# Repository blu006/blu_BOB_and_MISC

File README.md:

This repository contains my random items that I probably only produced once or twice.

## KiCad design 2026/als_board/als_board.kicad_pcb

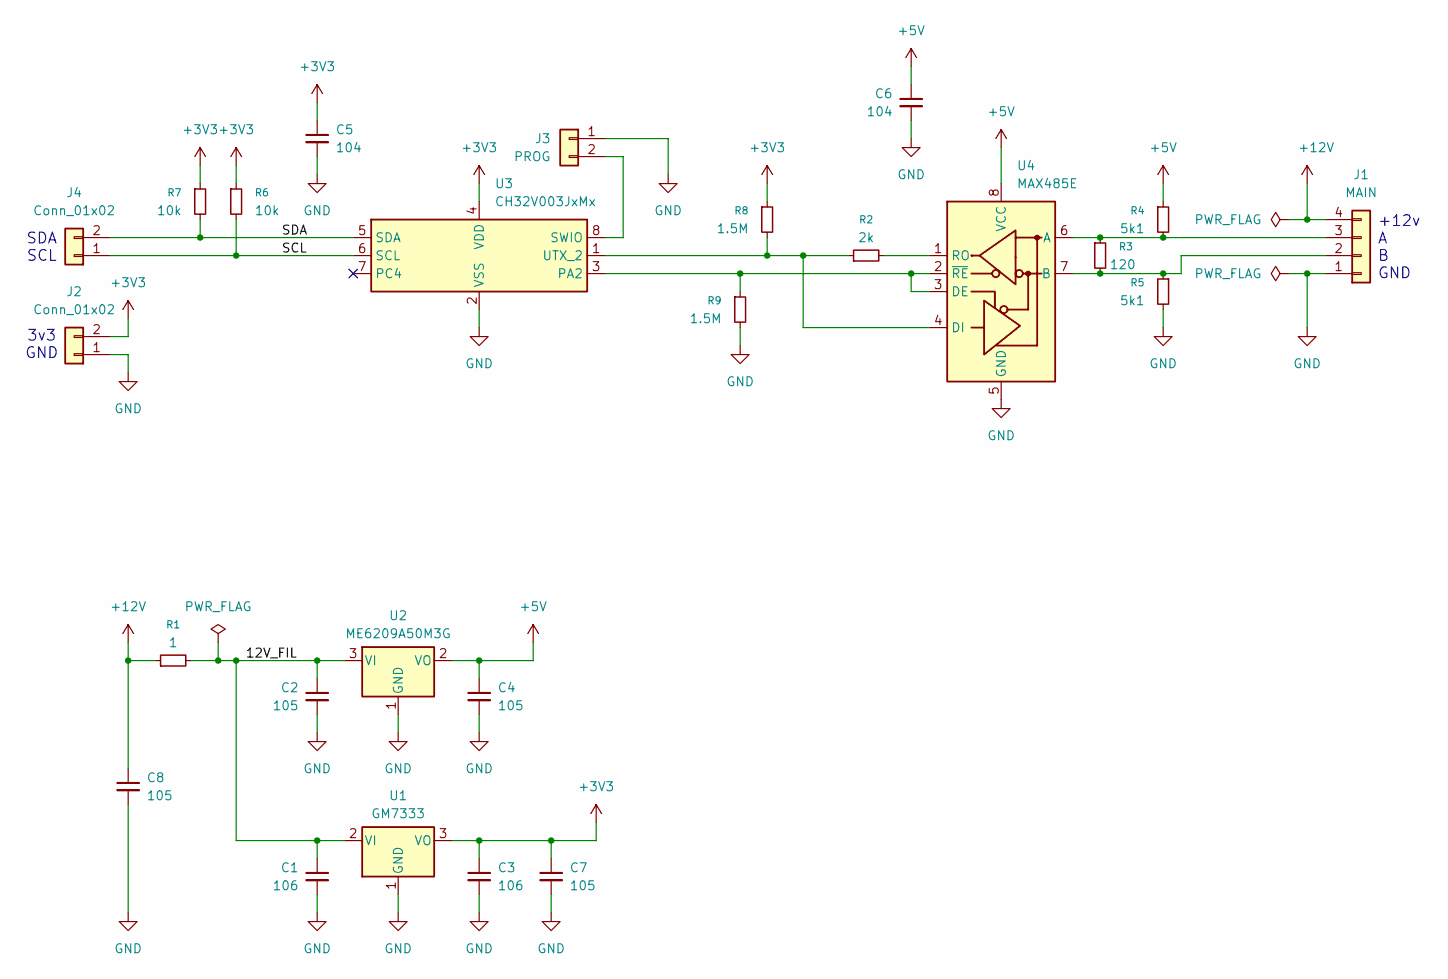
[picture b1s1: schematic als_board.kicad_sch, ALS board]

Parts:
C1, C3: 106; C_1206_3216Metric
C2, C4, C7, C8: 105; C_0805_2012Metric
C5, C6: 104; C_0603_1608Metric
J1: MAIN; PADS_4
J2: Conn_01x02; R_1206_3216Metric
J3: PROG; C_0805_2012Metric
J4: Conn_01x02; R_0805_2012Metric
R1: 1; R_0603_1608Metric
R2: 2k; R_0603_1608Metric
R3: 120; R_0603_1608Metric
R4, R5: 5k1; R_0603_1608Metric
R6, R7: 10k; R_0603_1608Metric
R8, R9: 1.5M; R_0603_1608Metric
U1: GM7333; SOT-89-3
U2: ME6209A50M3G; SOT-23
U3: CH32V003JxMx; JEITA_SOIC-8_3.9x4.9mm_P1.27mm
U4: MAX485E; SOIC-8_3.9x4.9mm_P1.27mm

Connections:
+3V3: C3.1, C5.1, C7.1, J2.2, R6.1, R7.1, R8.1, U1.3 (VO), U3.4 (VDD)
+5V: C4.1, C6.1, R4.1, U2.2 (VO), U4.8 (VCC)
+12V: C8.1, J1.4, R1.1
/12V_FIL: C1.1, C2.1, R1.2, U1.2 (VI), U2.3 (VI)
/SCL: J4.1, R6.2, U3.6 (SCL)
/SDA: J4.2, R7.2, U3.5 (SDA)
GND: C1.2, C2.2, C3.2, C4.2, C5.2, C6.2, C7.2, C8.2, J1.1, J2.1, J3.1, R5.2, R9.2, U1.1 (GND), U2.1 (GND), U3.2 (VSS), U4.5 (GND)
unnamed: J1.2, R3.2, R5.1, U4.7 (B)
unnamed: J1.3, R3.1, R4.2, U4.6 (A)
unnamed: J3.2, U3.8 (SWIO)
unnamed: R9.1, U3.3 (PA2), U4.2 (~RE), U4.3 (DE)
unnamed: R2.1, R8.2, U3.1 (UTX_2), U4.4 (DI)
unnamed: R2.2, U4.1 (RO)

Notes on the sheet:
3v3 GND
+12v A B GND
SDA SCL

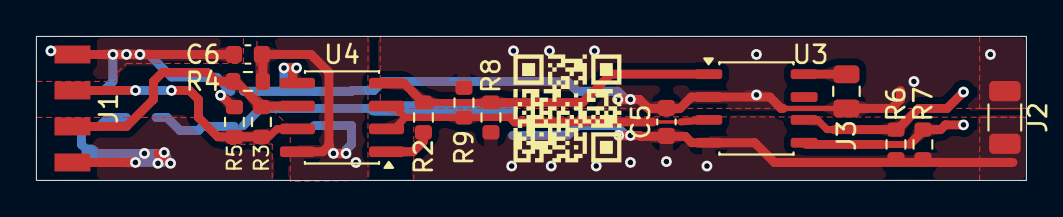
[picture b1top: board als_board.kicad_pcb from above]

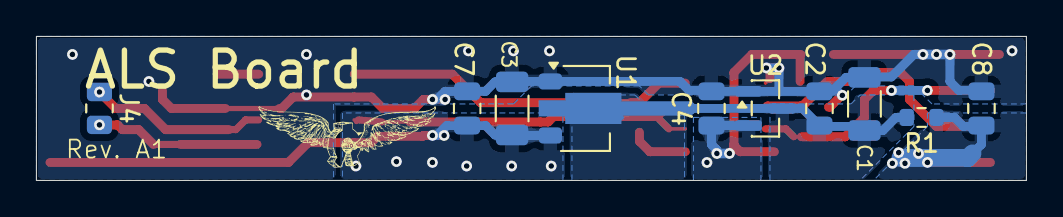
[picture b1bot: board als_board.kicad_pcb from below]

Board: 2 copper layers, 55.0 x 8.0 mm, 25 parts (10 on the bottom side), 13 nets.

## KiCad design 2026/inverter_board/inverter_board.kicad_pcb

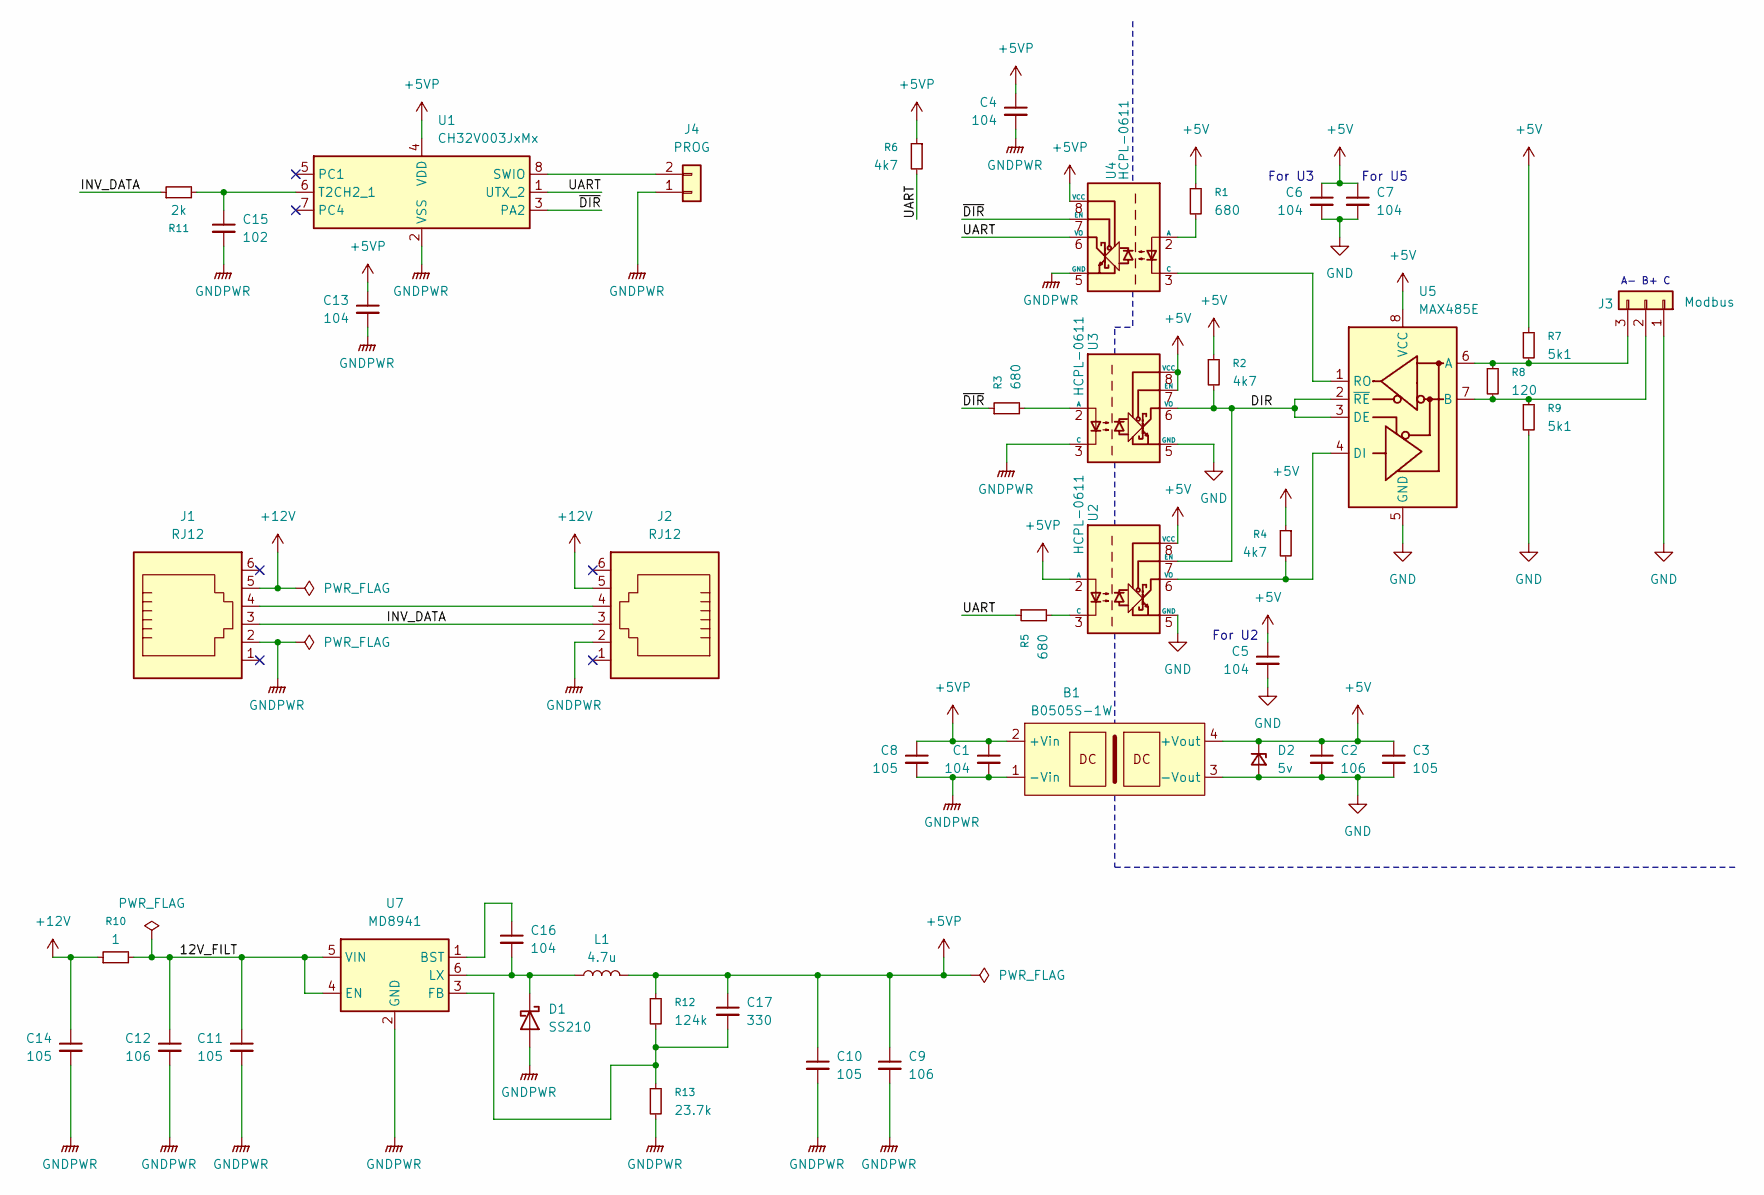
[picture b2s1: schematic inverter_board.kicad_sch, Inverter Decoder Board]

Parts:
B1: B0505S-1W; BxxxxS-1W
C1, C4, C5, C6, C7, C13, C16: 104; C_0603_1608Metric
C2, C9, C12: 106; C_1206_3216Metric
C3, C8, C10, C11, C14: 105; C_0805_2012Metric
C15: 102; C_0603_1608Metric
C17: 330; C_0603_1608Metric
D1: SS210; D_SMA
D2: 5v; D_SMB
J1, J2: RJ12; RJ25_Wayconn_MJEA-660X1_Horizontal
J3: Modbus; TerminalBlock_Phoenix_MKDS-3-3-5.08_1x03_P5.08mm_Horizontal
J4: PROG; R_0805_2012Metric
L1: 4.7u; L_APV_APH0420
R1, R3, R5: 680; R_0603_1608Metric
R2, R4, R6: 4k7; R_0603_1608Metric
R7, R9: 5k1; R_0603_1608Metric
R8: 120; R_0603_1608Metric
R10: 1; R_0603_1608Metric
R11: 2k; R_0603_1608Metric
R12: 124k; R_0603_1608Metric
R13: 23.7k; R_0603_1608Metric
U1: CH32V003JxMx; JEITA_SOIC-8_3.9x4.9mm_P1.27mm
U2, U3, U4: HCPL-0611; SOIC-8_3.9x4.9mm_P1.27mm
U5: MAX485E; SOIC-8_3.9x4.9mm_P1.27mm
U7: MD8941; SOT-23-6

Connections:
+5V: B1.4 (+Vout), C2.1, C3.1, C5.1, C6.1, C7.1, D2.1 (K), R1.1, R2.1, R4.1, R7.1, U2.8 (VCC), U3.7 (EN), U3.8 (VCC), U5.8 (VCC)
+5VP: B1.2 (+Vin), C1.1, C4.1, C8.1, C9.1, C10.1, C13.1, C17.1, L1.2, R6.1, R12.1, U1.4 (VDD), U2.2 (A), U4.8 (VCC)
+12V: C14.1, J1.5, J2.5, R10.1
/12V_FILT: C11.1, C12.1, R10.2, U7.4 (EN), U7.5 (VIN)
/DIR: R2.2, U2.7 (EN), U3.6 (VO), U5.2 (~RE), U5.3 (DE)
/INV_DATA: J1.3, J2.3, R11.1
/UART: R5.1, R6.2, U1.1 (UTX_2), U4.6 (VO)
/~DIR: R3.1, U1.3 (PA2), U4.7 (EN)
GND: B1.3 (-Vout), C2.2, C3.2, C5.2, C6.2, C7.2, D2.2 (A), J3.1, R9.2, U2.5 (GND), U3.5 (GND), U5.5 (GND)
GNDPWR: B1.1 (-Vin), C1.2, C4.2, C8.2, C9.2, C10.2, C11.2, C12.2, C13.2, C14.2, C15.2, D1.2 (A), J1.2, J2.2, J4.1, R13.2, U1.2 (VSS), U3.3 (C), U4.5 (GND), U7.2 (GND)
unnamed: C16.2, D1.1 (K), L1.1, U7.6 (LX)
unnamed: J1.4, J2.4
unnamed: J3.2, R8.2, R9.1, U5.7 (B)
unnamed: J3.3, R7.2, R8.1, U5.6 (A)
unnamed: J4.2, U1.8 (SWIO)
unnamed: C15.1, R11.2, U1.6 (T2CH2_1)
unnamed: R5.2, U2.3 (C)
unnamed: R4.2, U2.6 (VO), U5.4 (DI)
unnamed: R3.2, U3.2 (A)
unnamed: R1.2, U4.2 (A)
unnamed: U4.3 (C), U5.1 (RO)
unnamed: C16.1, U7.1 (BST)
unnamed: C17.2, R12.2, R13.1, U7.3 (FB)

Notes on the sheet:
For U5
For U3
A- B+ C
For U2

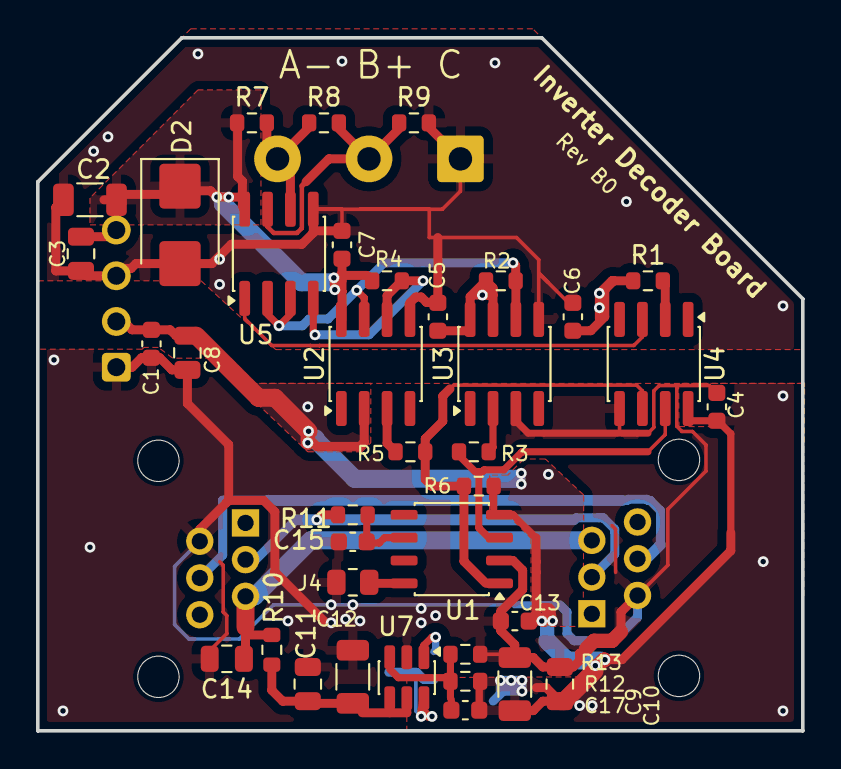
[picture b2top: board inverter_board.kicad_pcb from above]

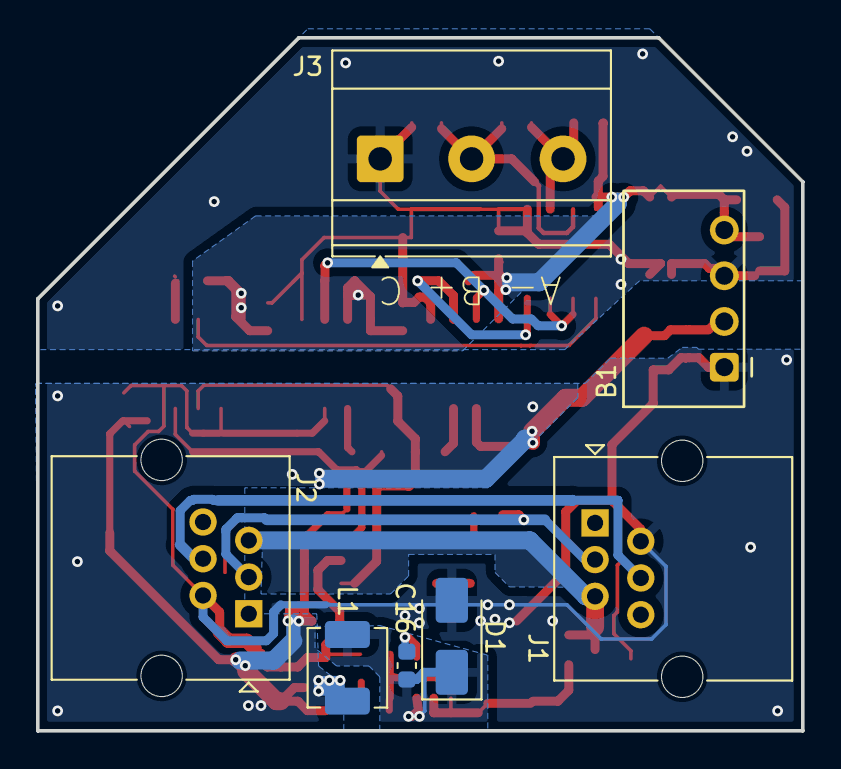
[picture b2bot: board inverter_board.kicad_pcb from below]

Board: 2 copper layers, 42.5 x 38.5 mm, 44 parts (7 on the bottom side), 23 nets.

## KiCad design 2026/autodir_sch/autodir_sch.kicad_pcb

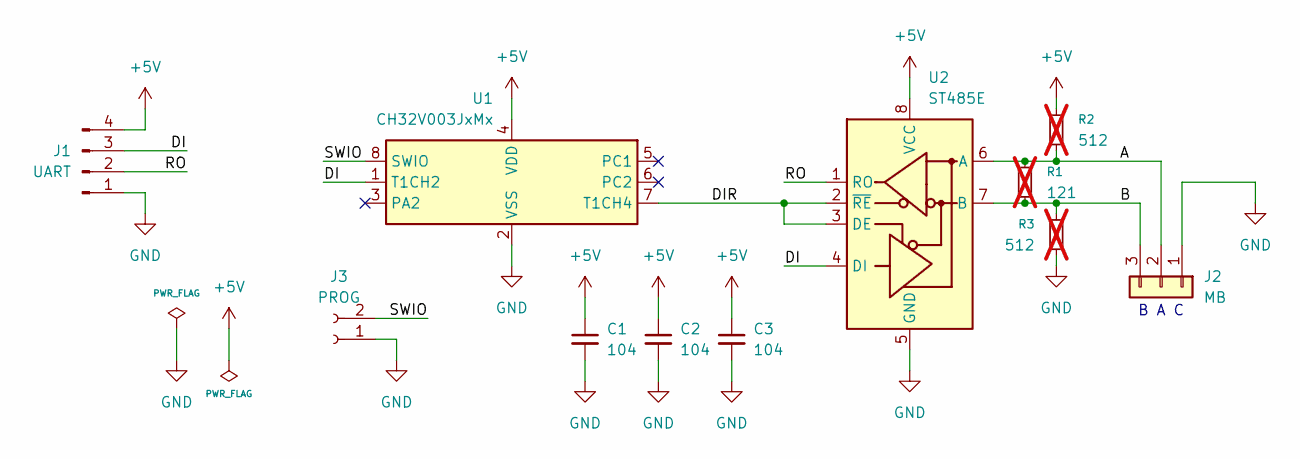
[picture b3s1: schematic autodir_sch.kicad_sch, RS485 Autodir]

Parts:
C1, C2, C3: 104; C_0603_1608Metric
J1: UART; PinHeader_1x04_P2.54mm_Horizontal
J2: MB; TerminalBlock_Phoenix_MKDS-1,5-3-5.08_1x03_P5.08mm_Horizont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
J3: PROG; R_0805_2012Metric
R1: 121; R_0603_1608Metric; not fitted
R2, R3: 512; R_0603_1608Metric; not fitted
U1: CH32V003JxMx; JEITA_SOIC-8_3.9x4.9mm_P1.27mm
U2: ST485E; SOIC-8_3.9x4.9mm_P1.27mm

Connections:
+5V: C1.1, C2.1, C3.1, J1.4, R2.1, U1.4 (VDD), U2.8 (VCC)
/A: J2.2, R1.1, R2.2, U2.6 (A)
/B: J2.3, R1.2, R3.1, U2.7 (B)
/DI: J1.3, U1.1 (T1CH2), U2.4 (DI)
/DIR: U1.7 (T1CH4), U2.2 (~RE), U2.3 (DE)
/RO: J1.2, U2.1 (RO)
/SWIO: J3.2, U1.8 (SWIO)
GND: C1.2, C2.2, C3.2, J1.1, J2.1, J3.1, R3.2, U1.2 (VSS), U2.5 (GND)

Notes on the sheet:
B A C

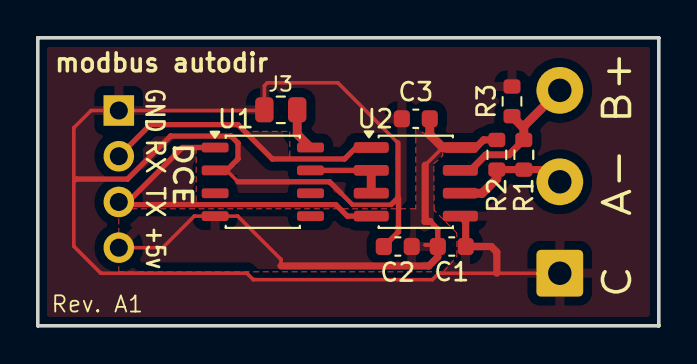
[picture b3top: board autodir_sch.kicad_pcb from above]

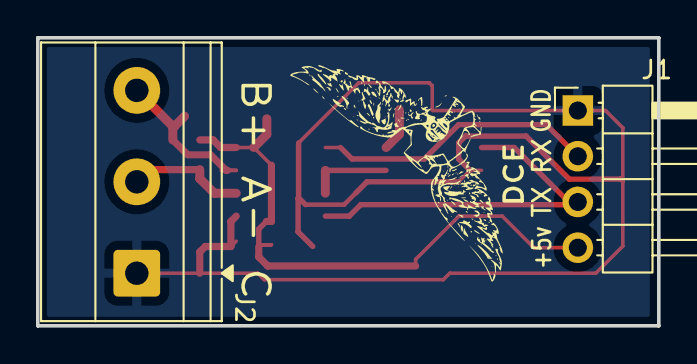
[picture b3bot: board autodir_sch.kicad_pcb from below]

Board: 2 copper layers, 34.5 x 16.0 mm, 11 parts (2 on the bottom side), 8 nets.

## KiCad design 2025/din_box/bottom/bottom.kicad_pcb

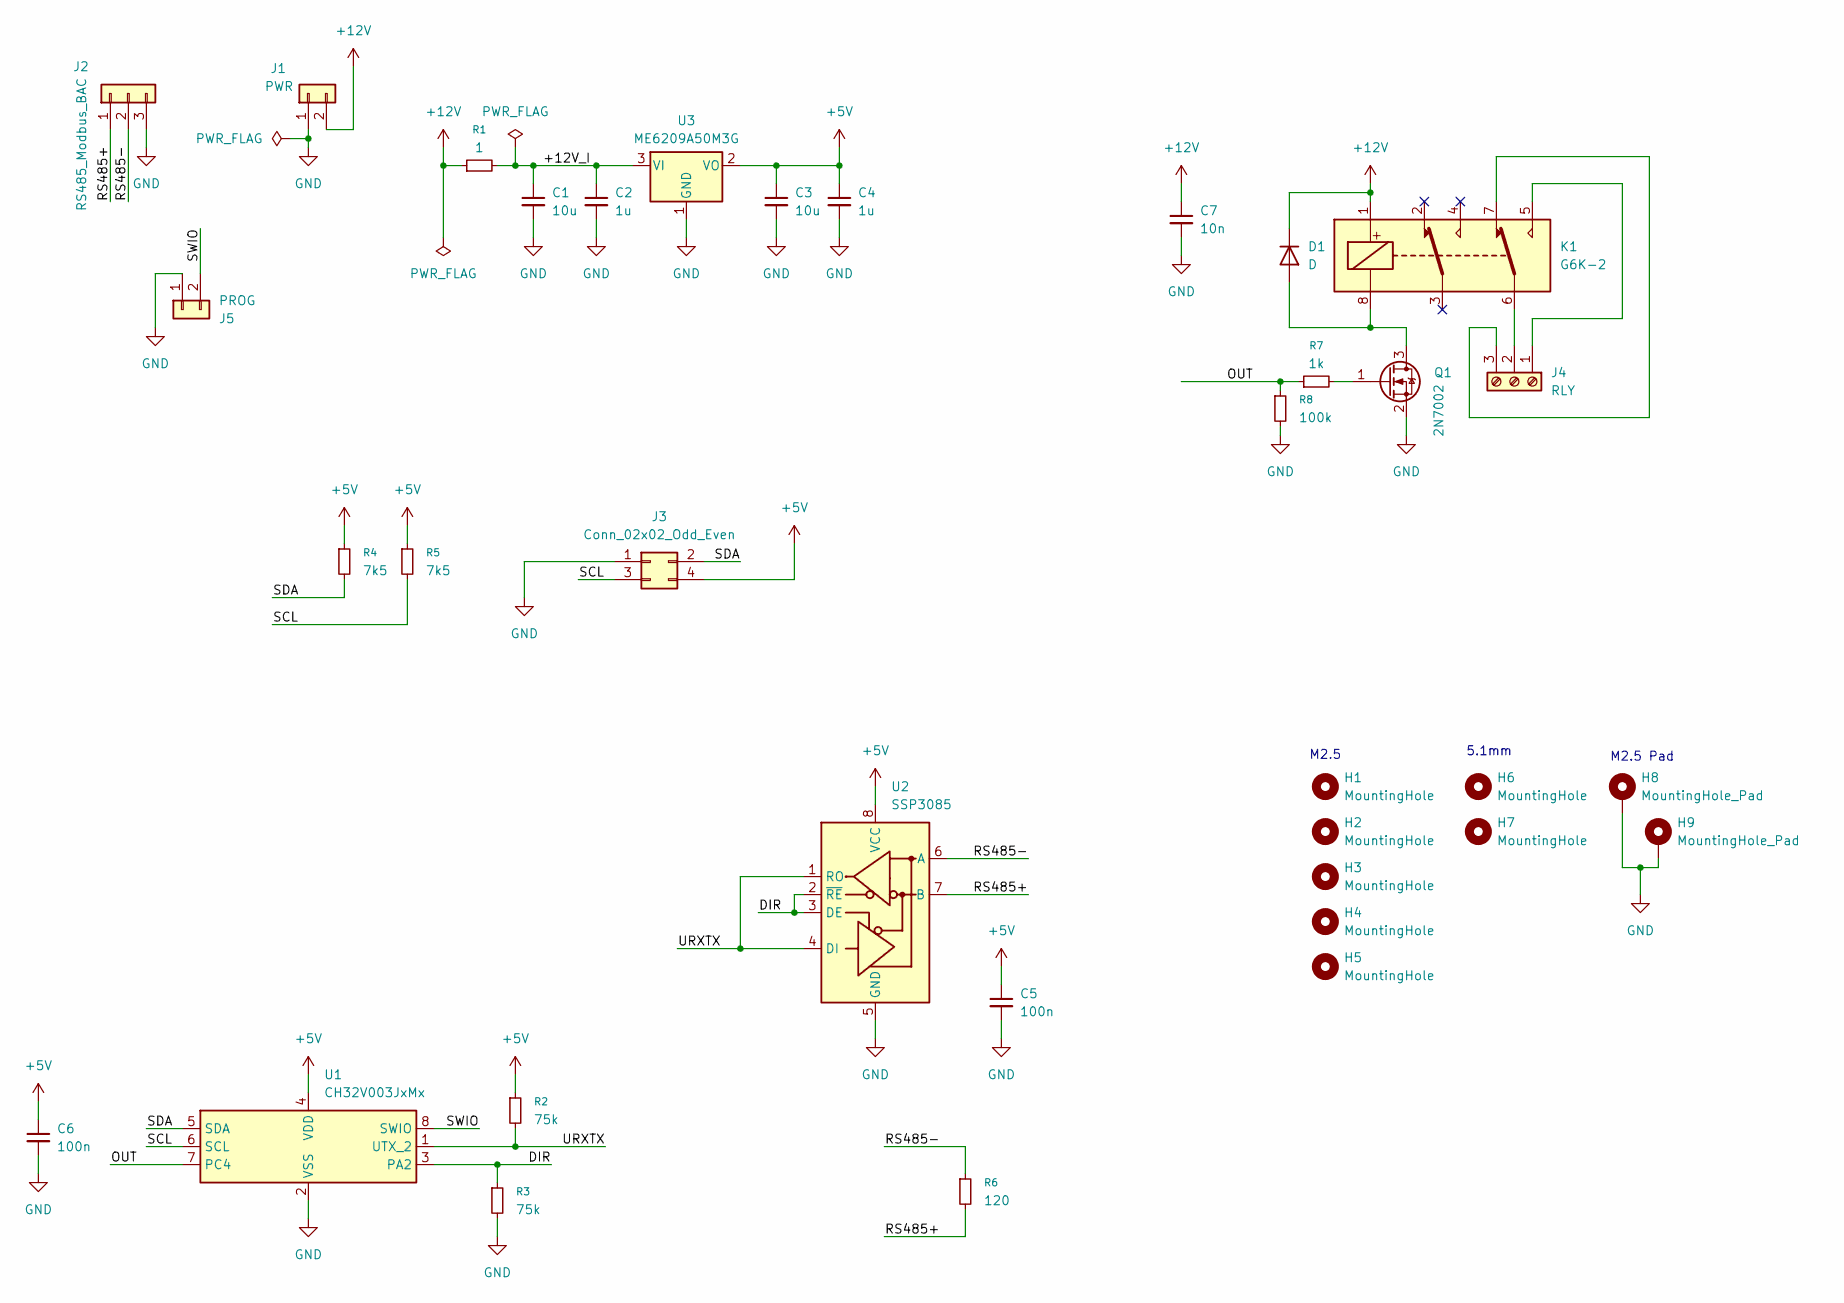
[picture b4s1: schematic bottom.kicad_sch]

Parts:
C1, C3: 10u; C_1206_3216Metric
C2, C4: 1u; C_0805_2012Metric
C5, C6: 100n; C_0603_1608Metric
C7: 10n; C_0603_1608Metric
D1: D; D_MELF
H1, H2, H3, H4, H5: MountingHole; MountingHole_2.7mm_M2.5_ISO7380
H6, H7: MountingHole; MountingHole_5.3mm_M5_ISO7380
H8, H9: MountingHole_Pad; MountingHole_2.7mm_M2.5_ISO7380_Pad
J1: PWR; TerminalBlock_Phoenix_MKDS-1,5-2-5.08_1x02_P5.08mm_Horizont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
J2: RS485_Modbus_BAC; TerminalBlock_Phoenix_MKDS-1,5-3-5.08_1x03_P5.08mm_Horizont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
J3: Conn_02x02_Odd_Even; PinHeader_2x02_P2.54mm_Vertical
J4: RLY; TerminalBlock_Phoenix_MKDS-1,5-3-5.08_1x03_P5.08mm_Horizont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
J5: PROG; PinHeader_1x02_P2.54mm_Vertical
K1: G6K-2; Relay_DPDT_Omron_G6K-2F-Y
Q1: 2N7002; SOT-23
R1: 1; R_0603_1608Metric
R2, R3: 75k; R_0603_1608Metric
R4, R5: 7k5; R_0603_1608Metric
R6: 120; R_0603_1608Metric
R7: 1k; R_0603_1608Metric
R8: 100k; R_0402_1005Metric
U1: CH32V003JxMx; SOP-8_3.9x4.9mm_P1.27mm
U2: SSP3085; SOIC-8_3.9x4.9mm_P1.27mm
U3: ME6209A50M3G; SOT-23

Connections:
+5V: C3.1, C4.1, C5.1, C6.1, J3.4, R2.1, R4.1, R5.1, U1.4 (VDD), U2.8 (VCC), U3.2 (VO)
+12V: C7.1, D1.1 (K), J1.2, K1.1, R1.1
/+12V_I: C1.1, C2.1, R1.2, U3.3 (VI)
/DIR: R3.1, U1.3 (PA2), U2.2 (~RE), U2.3 (DE)
/OUT: R7.1, R8.1, U1.7 (PC4)
/RS485+: J2.1, R6.2, U2.7 (B)
/RS485-: J2.2, R6.1, U2.6 (A)
/SCL: J3.3, R5.2, U1.6 (SCL)
/SDA: J3.2, R4.2, U1.5 (SDA)
/SWIO: J5.2, U1.8 (SWIO)
/URXTX: R2.2, U1.1 (UTX_2), U2.1 (RO), U2.4 (DI)
GND: C1.2, C2.2, C3.2, C4.2, C5.2, C6.2, C7.2, H8.1, H9.1, J1.1, J2.3, J3.1, J5.1, Q1.2 (S), R3.2, R8.2, U1.2 (VSS), U2.5 (GND), U3.1 (GND)
unnamed: D1.2 (A), K1.8, Q1.3 (D)
unnamed: J4.1, K1.5
unnamed: J4.2, K1.6
unnamed: J4.3, K1.7
unnamed: Q1.1 (G), R7.2

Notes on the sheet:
M2.5 Pad
5.1mm
M2.5

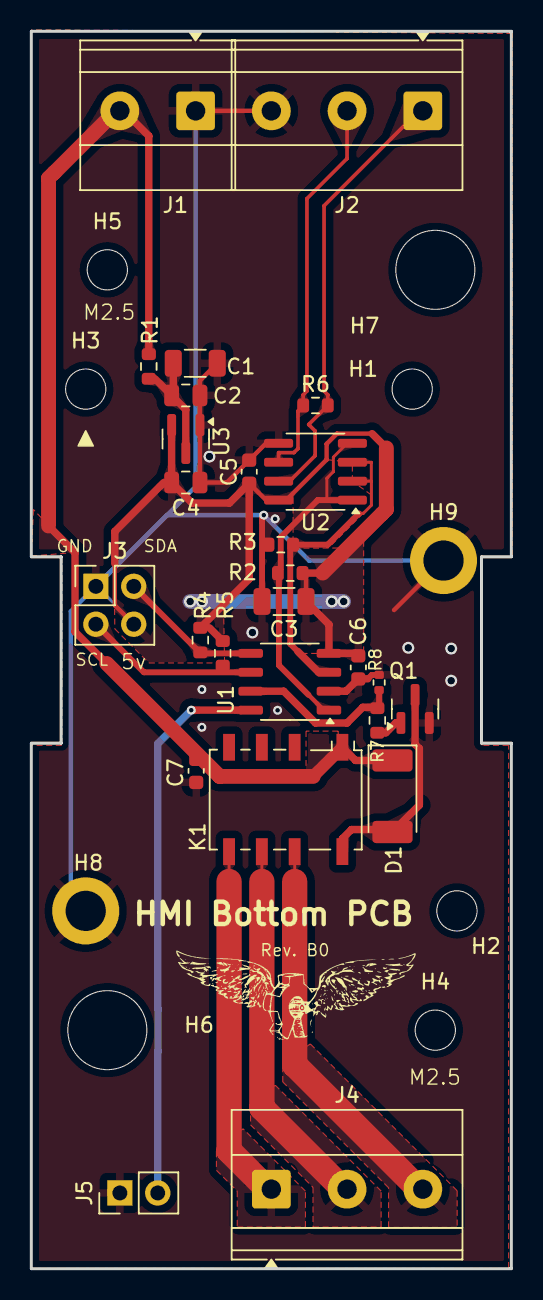
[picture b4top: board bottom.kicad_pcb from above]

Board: 2 copper layers, 32.2 x 83.0 mm, 36 parts (1 on the bottom side), 17 nets.

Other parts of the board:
QR1: MAGLab Website

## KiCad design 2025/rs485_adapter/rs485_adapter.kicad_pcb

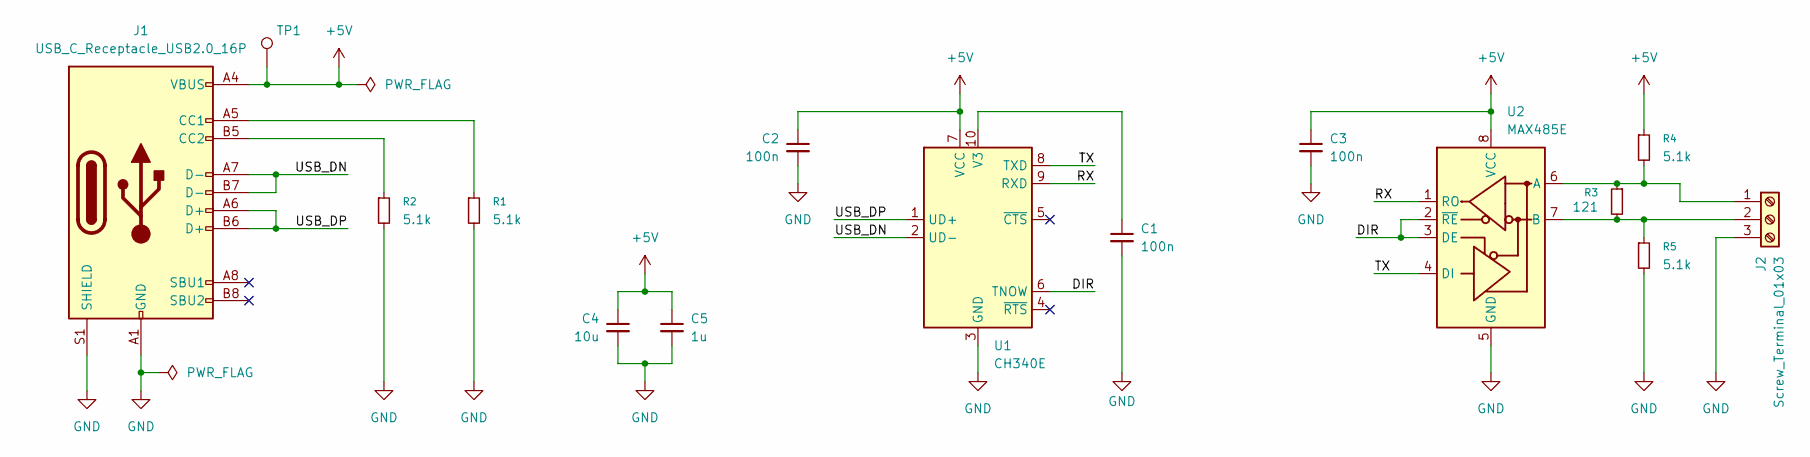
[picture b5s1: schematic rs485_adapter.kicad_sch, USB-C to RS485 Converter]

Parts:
C1, C2, C3: 100n; C_0603_1608Metric
C4: 10u; C_1206_3216Metric
C5: 1u; C_0805_2012Metric
J1: USB_C_Receptacle_USB2.0_16P; USB_C_Receptacle_XKB_U262-16XN-4BVC11
J2: Screw_Terminal_01x03; TerminalBlock_Phoenix_MKDS-1,5-3-5.08_1x03_P5.08mm_Horizont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
R1, R2, R4, R5: 5.1k; R_0603_1608Metric
R3: 121; R_0603_1608Metric
TP1: TestPoint; TestPoint_Pad_1.0x1.0mm
U1: CH340E; MSOP-10_3x3mm_P0.5mm
U2: MAX485E; SOIC-8_3.9x4.9mm_P1.27mm

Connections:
+5V: C2.1, C3.1, C4.1, C5.1, J1.A4 (VBUS), J1.A9 (VBUS), J1.B4 (VBUS), J1.B9 (VBUS), R4.1, TP1.1, U1.7 (VCC), U2.8 (VCC)
/DIR: U1.6 (TNOW), U2.2 (~RE), U2.3 (DE)
/RX: U1.9 (RXD), U2.1 (RO)
/TX: U1.8 (TXD), U2.4 (DI)
/USB_DN: J1.A7 (D-), J1.B7 (D-), U1.2 (UD-)
/USB_DP: J1.A6 (D+), J1.B6 (D+), U1.1 (UD+)
GND: C1.2, C2.2, C3.2, C4.2, C5.2, J1.A1 (GND), J1.A12 (GND), J1.B1 (GND), J1.B12 (GND), J1.S1 (SHIELD), J2.3, R1.2, R2.2, R5.2, U1.3 (GND), U2.5 (GND)
unnamed: J1.A5 (CC1), R1.1
unnamed: J1.B5 (CC2), R2.1
unnamed: J2.1, R3.1, R4.2, U2.6 (A)
unnamed: J2.2, R3.2, R5.1, U2.7 (B)
unnamed: C1.1, U1.10 (V3)

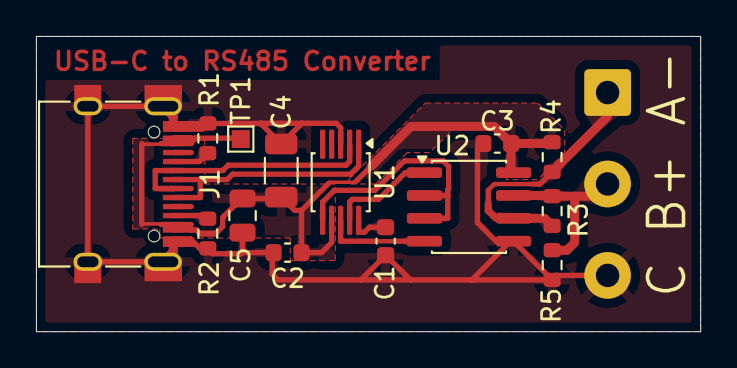
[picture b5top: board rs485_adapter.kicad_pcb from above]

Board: 2 copper layers, 36.9 x 16.4 mm, 15 parts (1 on the bottom side), 12 nets.

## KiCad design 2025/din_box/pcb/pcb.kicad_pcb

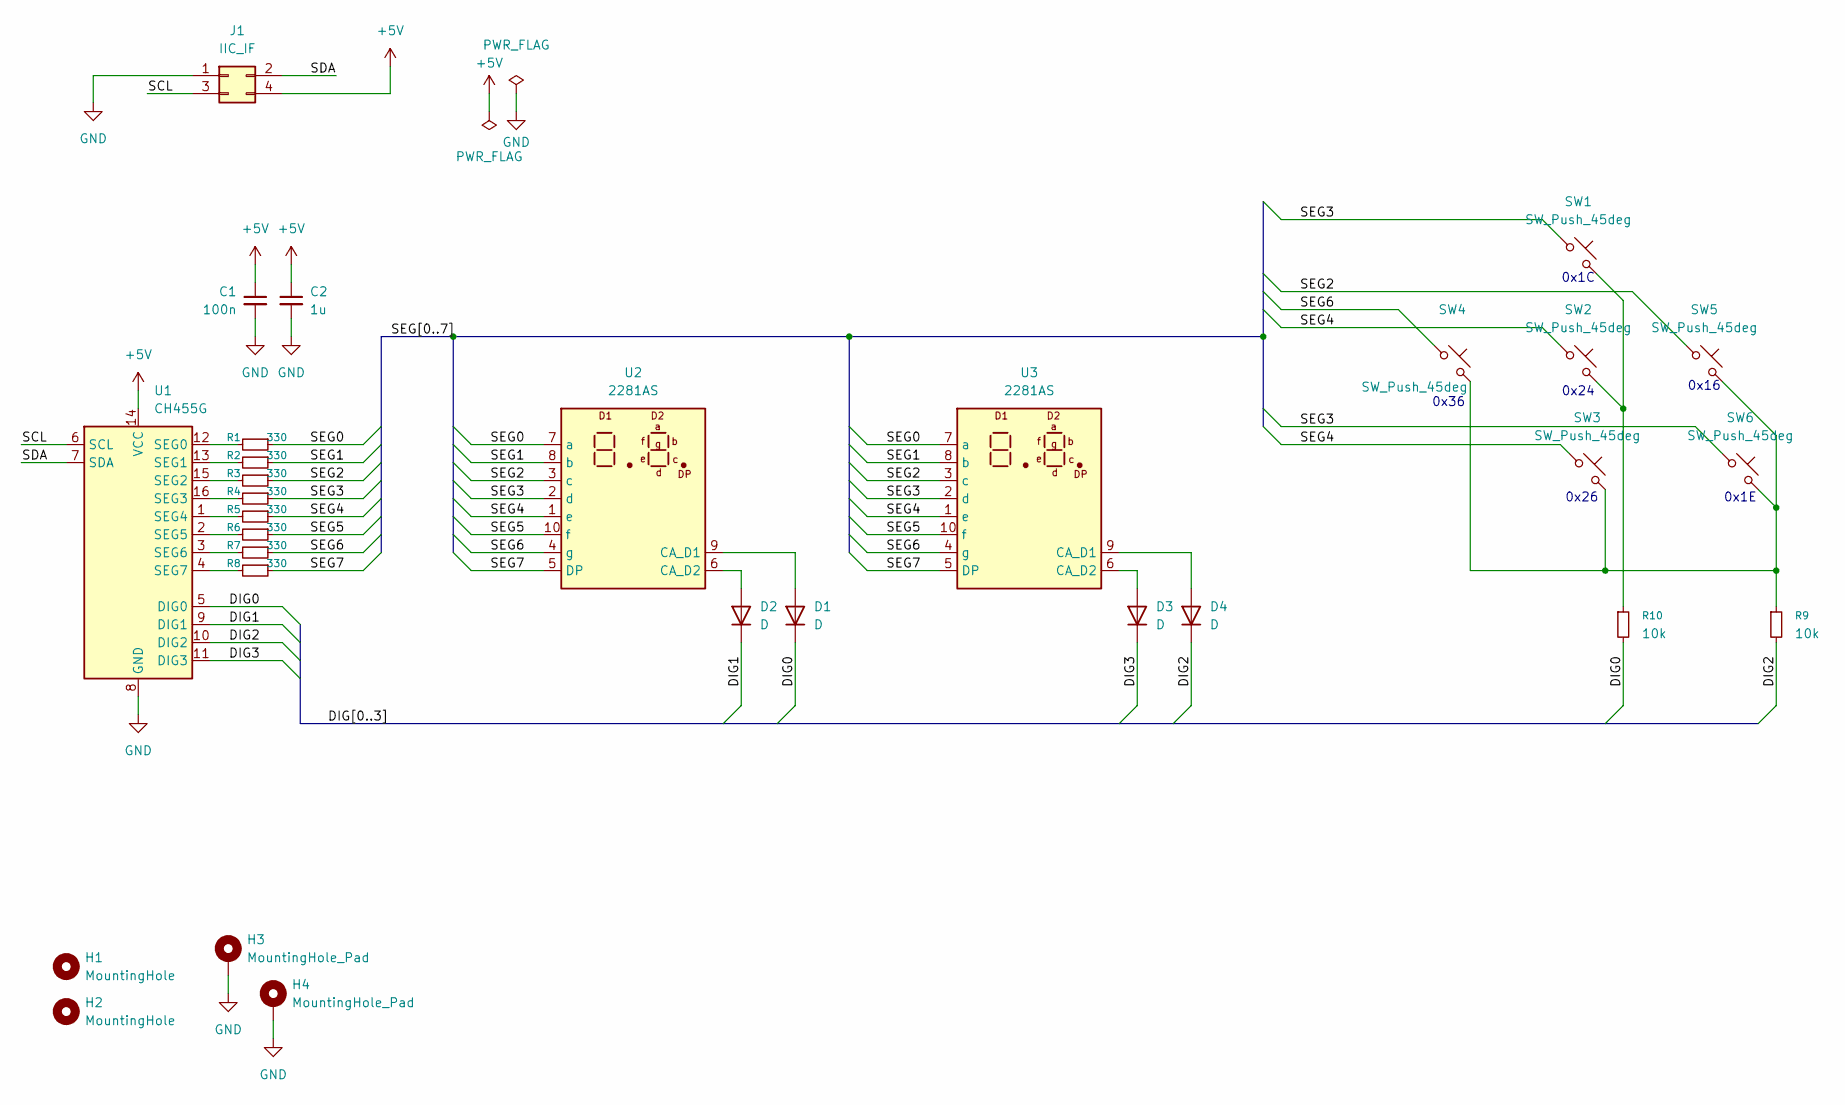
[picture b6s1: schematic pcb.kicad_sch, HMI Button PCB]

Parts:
C1: 100n; C_0603_1608Metric
C2: 1u; C_0805_2012Metric
D1, D2, D3, D4: D; D_SOD-323
H1, H2: MountingHole; MountingHole_2.7mm_M2.5_ISO7380
H3, H4: MountingHole_Pad; MountingHole_2.7mm_M2.5_ISO14580_Pad_TopBottom
J1: IIC_IF; PinSocket_2x02_P2.54mm_Vertical
R1, R2, R3, R4, R5, R6, R7, R8: 330; R_0603_1608Metric
R9, R10: 10k; R_0603_1608Metric
SW1, SW2, SW3, SW4, SW5, SW6: SW_Push_45deg; SW_SPST_PTS810
U1: CH455G; SOP-16_3.9x9.9mm_P1.27mm
U2, U3: 2281AS; 7seg_2dig

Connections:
+5V: C1.1, C2.1, J1.4, U1.14 (VCC)
/DIG0: D1.1 (K), R10.2, U1.5 (DIG0)
/DIG1: D2.1 (K), U1.9 (DIG1)
/DIG2: D4.1 (K), R9.2, U1.10 (DIG2)
/DIG3: D3.1 (K), U1.11 (DIG3)
/SCL: J1.3, U1.6 (SCL)
/SDA: J1.2, U1.7 (SDA)
/SEG0: R1.1, U2.7 (a), U3.7 (a)
/SEG1: R2.1, U2.8 (b), U3.8 (b)
/SEG2: R3.1, SW5.1, U2.3 (c), U3.3 (c)
/SEG3: R4.1, SW1.1, SW6.1, U2.2 (d), U3.2 (d)
/SEG4: R5.1, SW2.1, SW3.1, U2.1 (e), U3.1 (e)
/SEG5: R6.1, U2.10 (f), U3.10 (f)
/SEG6: R7.1, SW4.1, U2.4 (g), U3.4 (g)
/SEG7: R8.1, U2.5 (DP), U3.5 (DP)
GND: C1.2, C2.2, H3.1, H4.1, J1.1, U1.8 (GND)
unnamed: D1.2 (A), U2.9 (CA_D1)
unnamed: D2.2 (A), U2.6 (CA_D2)
unnamed: D3.2 (A), U3.6 (CA_D2)
unnamed: D4.2 (A), U3.9 (CA_D1)
unnamed: R9.1, SW3.2, SW4.2, SW5.2, SW6.2
unnamed: R10.1, SW1.2, SW2.2
unnamed: R1.2, U1.12 (SEG0)
unnamed: R2.2, U1.13 (SEG1)
unnamed: R3.2, U1.15 (SEG2)
unnamed: R4.2, U1.16 (SEG3)
unnamed: R5.2, U1.1 (SEG4)
unnamed: R6.2, U1.2 (SEG5)
unnamed: R7.2, U1.3 (SEG6)
unnamed: R8.2, U1.4 (SEG7)

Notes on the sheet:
0x1E
0x26
0x36
0x1C
0x16
0x24

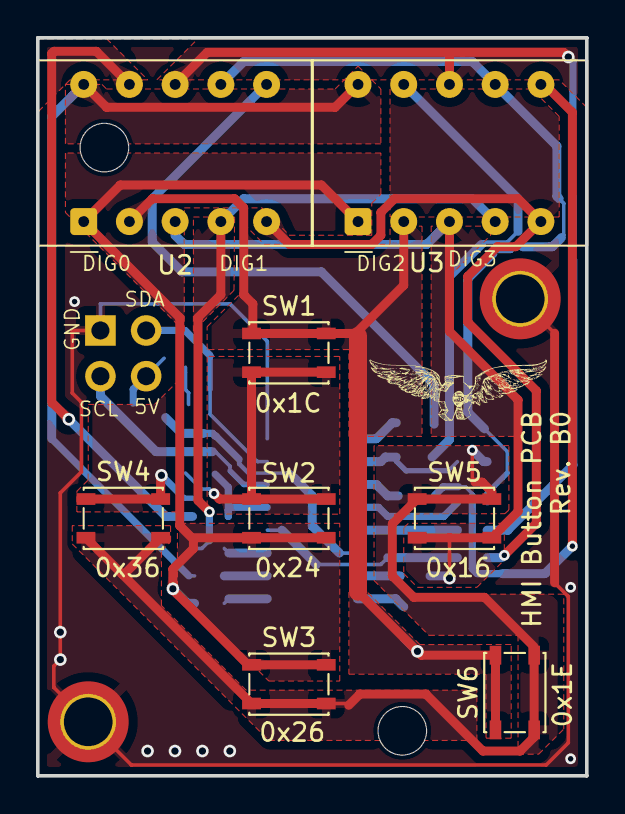
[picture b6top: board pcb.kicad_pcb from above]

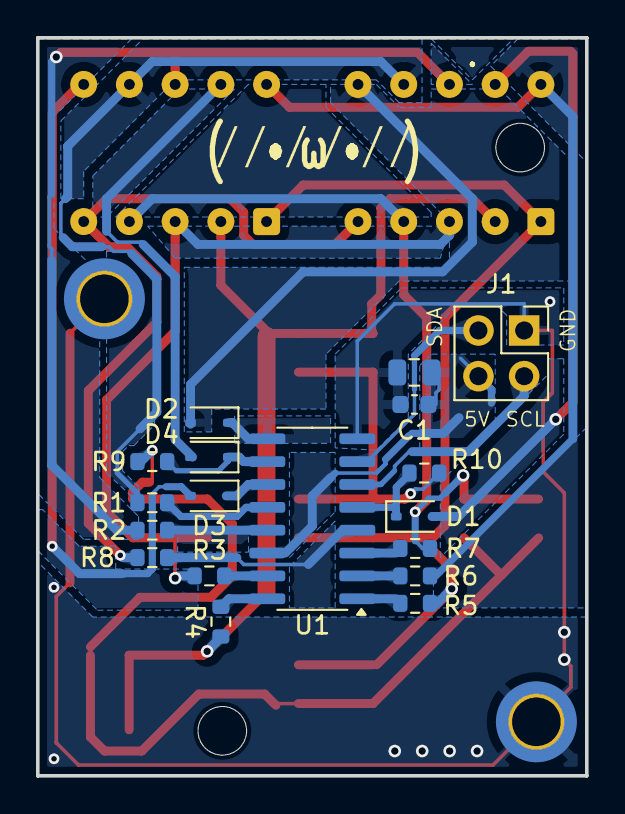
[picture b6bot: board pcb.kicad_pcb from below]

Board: 2 copper layers, 30.5 x 41.0 mm, 30 parts (19 on the bottom side), 30 nets.

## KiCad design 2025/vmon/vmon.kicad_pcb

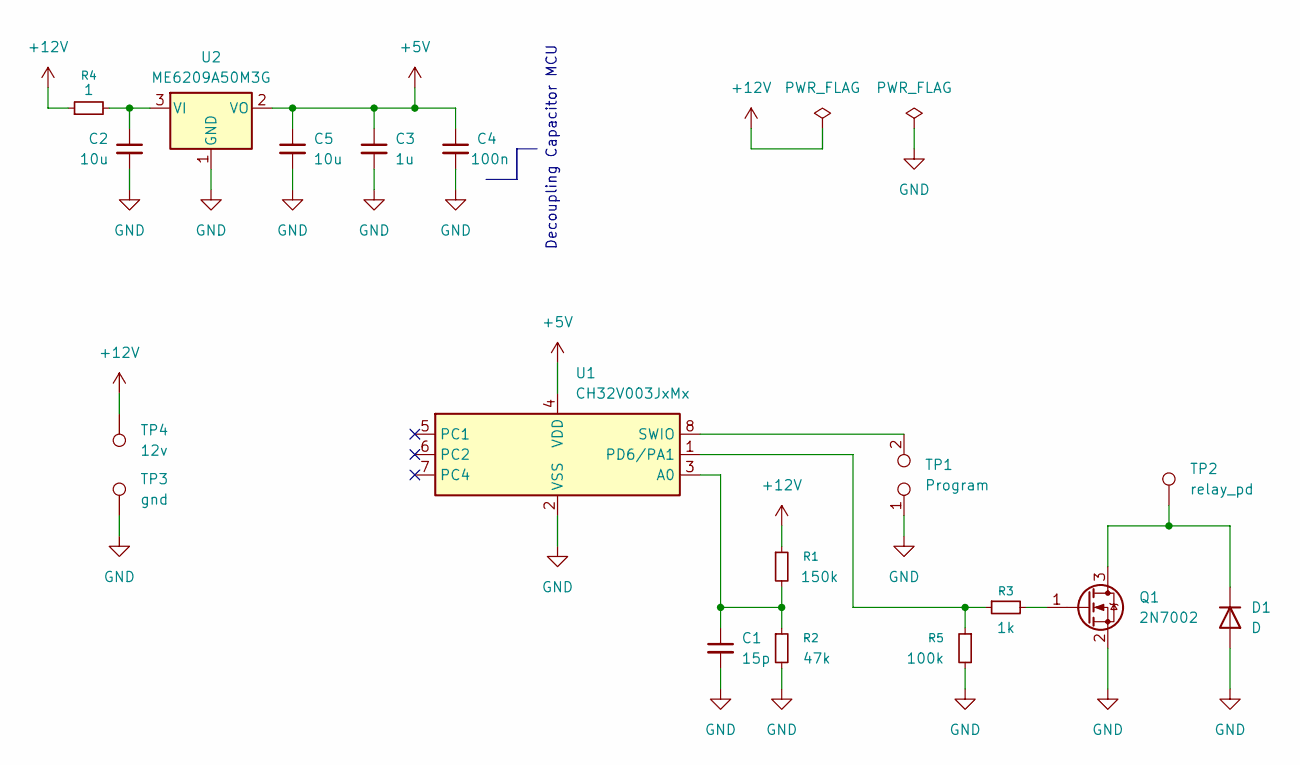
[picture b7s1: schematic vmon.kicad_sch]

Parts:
C1: 15p; C_0805_2012Metric
C2, C5: 10u; C_1206_3216Metric
C3: 1u; C_0805_2012Metric
C4: 100n; C_0603_1608Metric
D1: D; D_MELF
Q1: 2N7002; SOT-23
R1: 150k; R_0603_1608Metric
R2: 47k; R_0603_1608Metric
R3: 1k; R_0603_1608Metric
R4: 1; R_0603_1608Metric
R5: 100k; R_0603_1608Metric
TP1: Program; SolderJumper-2_P1.3mm_Open_Pad1.0x1.5mm
TP2: relay_pd; TestPoint_Pad_1.5x1.5mm
TP3: gnd; TestPoint_Pad_1.5x1.5mm
TP4: 12v; TestPoint_Pad_1.5x1.5mm
U1: CH32V003JxMx; SOP-8_3.9x4.9mm_P1.27mm
U2: ME6209A50M3G; SOT-23

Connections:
+5V: C3.1, C4.1, C5.1, U1.4 (VDD), U2.2 (VO)
+12V: R1.1, R4.1, TP4.1
GND: C1.2, C2.2, C3.2, C4.2, C5.2, D1.2 (A), Q1.2 (S), R2.2, R5.2, TP1.1, TP3.1, U1.2 (VSS), U2.1 (GND)
unnamed: D1.1 (K), Q1.3 (D), TP2.1
unnamed: Q1.1 (G), R3.2
unnamed: C1.1, R1.2, R2.1, U1.3 (A0)
unnamed: TP1.2, U1.8 (SWIO)
unnamed: R3.1, R5.1, U1.1 (PD6/PA1)
unnamed: C2.1, R4.2, U2.3 (VI)

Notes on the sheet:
Decoupling Capacitor MCU

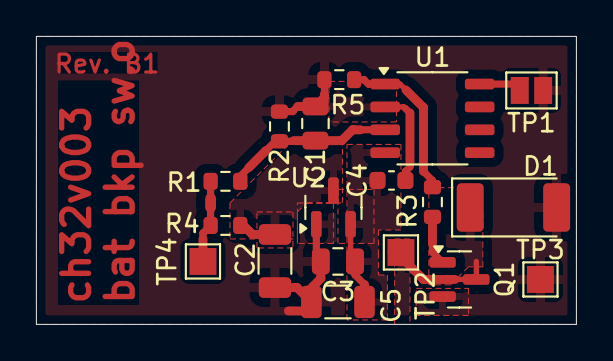
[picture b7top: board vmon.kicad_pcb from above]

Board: 2 copper layers, 30.0 x 16.0 mm, 18 parts (0 on the bottom side), 9 nets.

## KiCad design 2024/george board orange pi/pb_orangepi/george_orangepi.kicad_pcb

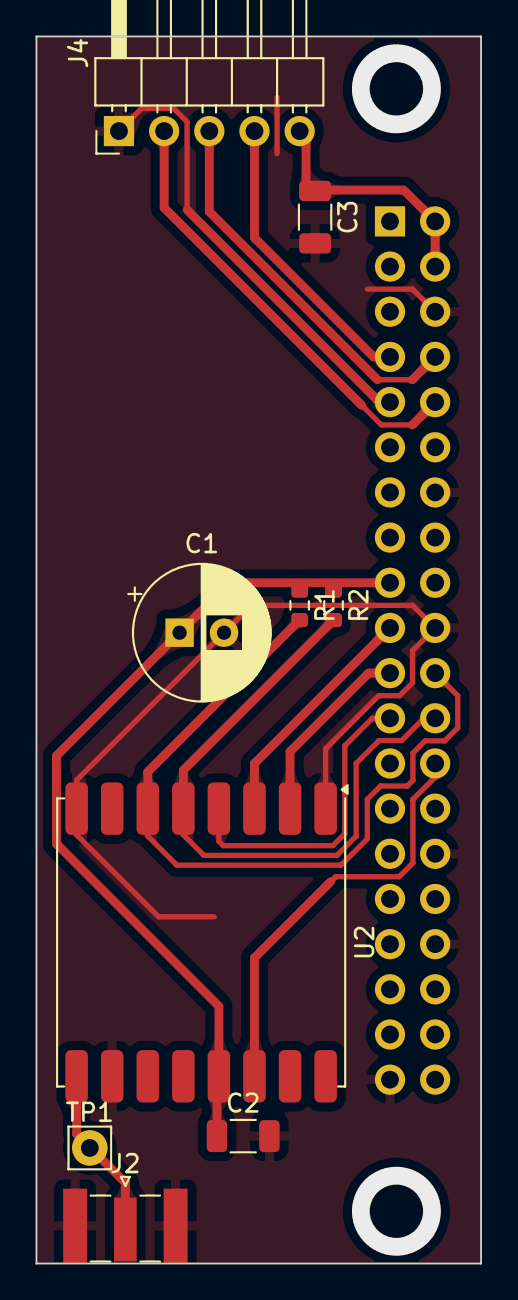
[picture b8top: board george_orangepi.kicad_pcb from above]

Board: 2 copper layers, 25.0 x 69.0 mm, 10 parts (1 on the bottom side), 13 nets.

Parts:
C1: 47uF; CP_Radial_D7.5mm_P2.50mm
C2, C3: 106; C_1206_3216Metric
J1: Conn_02x20_Odd_Even; PinSocket_2x20_P2.54mm_Vertical
J2: Conn_Coaxial; SMA_Samtec_SMA-J-P-X-ST-EM1_EdgeMount
J4: Conn_01x05_Pin; PinHeader_1x05_P2.54mm_Horizontal
R1, R2: 104; R_0603_1608Metric
TP1: TestPoint; TestPoint_THTPad_2.0x2.0mm_Drill1.0mm
U2: RFM95W-868S2; HOPERF_RFM9XW_SMD

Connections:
+3V3: C1.1, C2.1, J1.17, R1.1, R2.1, U2.13 (3.3V)
+5V: C3.1, J1.2, J1.4, J4.5
/IRQ: J1.26, U2.14 (DIO0)
/PPS_IN: J1.7, J4.4
/RESET: J1.22, R1.2, U2.6 (RESET)
/SPI0_CLK: J1.23, U2.4 (SCK)
/SPI0_CS0: J1.24, R2.2, U2.5 (NSS)
/SPI0_MISO: J1.21, U2.2 (MISO)
/SPI0_MOSI: J1.19, U2.3 (MOSI)
/U_RX: J1.10, J4.2
/U_TX: J1.8, J4.3
GND: C1.2, C2.2, C3.2, J1.6, J1.9, J1.14, J1.20, J1.30, J1.34, J1.39, J2.2 (Ext), J4.1, U2.1 (GND), U2.8 (GND), U2.10 (GND)
unnamed: J2.1 (In), TP1.1, U2.9 (ANT)
